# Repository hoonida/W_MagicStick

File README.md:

# MagicStick

## 1. Hardware

### [Arduino Pro Micro](https://www.sparkfun.com/products/12640)

| pin | func | name          |
|-----|------|---------------|
| 2   | DIN  | IR Receive    |
| 3   | DOUT | IR Send       |
| 7   | DIN  | Button        |
| 14  | DOUT | LED 0         |
| 15  | DOUT | LED 1         |
| 16  | DOUT | Relay         |
| 9   | PWM  | Speaker -     |
| 10  | PWM  | Speaker +     |
| A0  | AIN  | Potentiometer |

### Power
- Battery : LR45(1.5V) x 3EA
- Voltage : 4.5V
- Capacity : 45mAh

## 2. Software

### State Machine

| state    | task                             |
|----------|----------------------------------|
| waiting  | receive IR                       |
| sending  | send IR & blink LED & play sound |
| ceremony | blink LED                        |

### Dependencies
- [IRremote (3.6.1)](https://github.com/Arduino-IRremote/Arduino-IRremote)
- [TaskScheduler (3.6.0)](https://github.com/arkhipenko/TaskScheduler)

## 3. References
[NEC Infrared Transmission Protocol](https://techdocs.altium.com/display/FPGA/NEC+Infrared+Transmission+Protocol)

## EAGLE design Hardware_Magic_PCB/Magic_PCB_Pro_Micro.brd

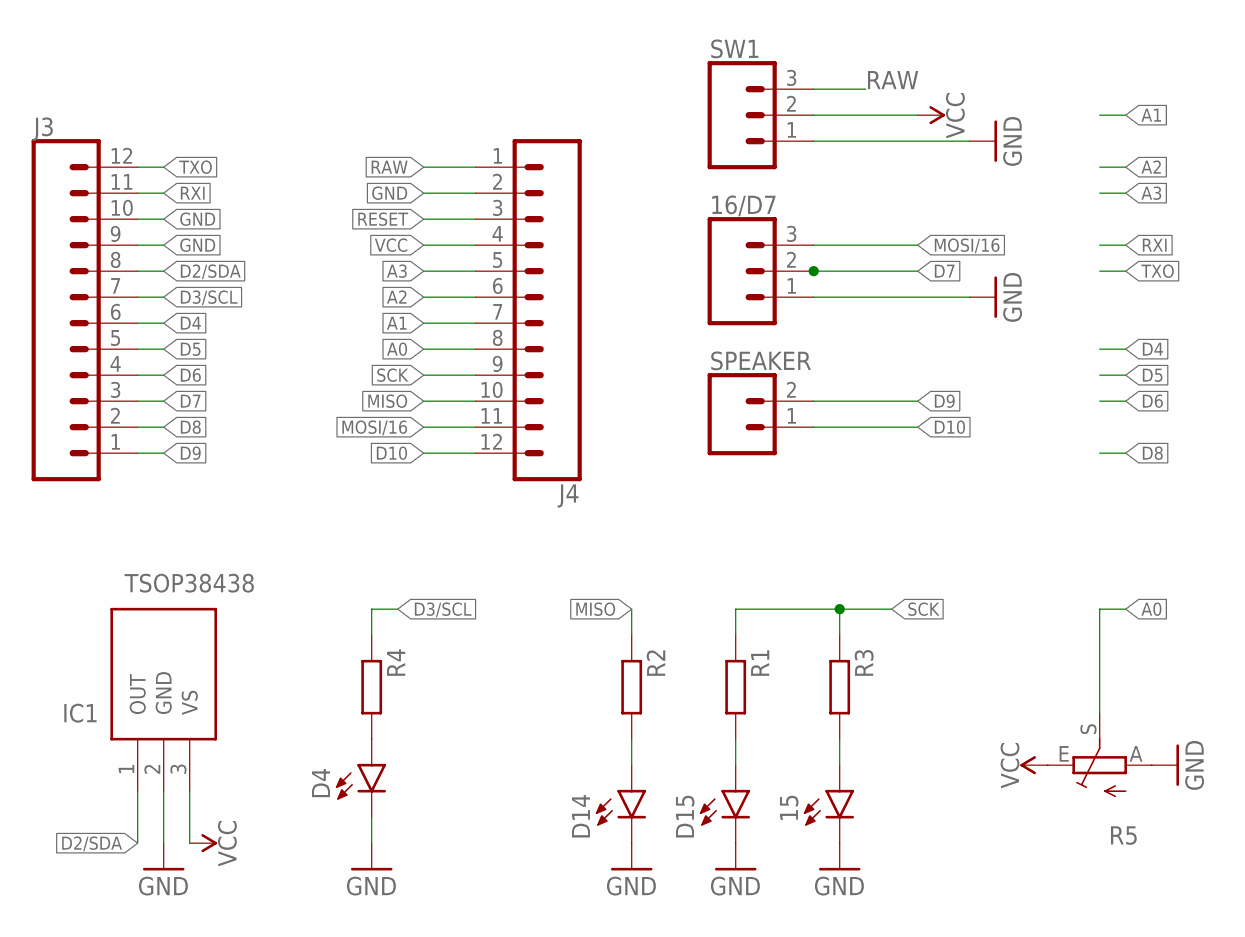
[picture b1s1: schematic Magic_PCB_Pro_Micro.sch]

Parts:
15: GREEN; SFH482
16/D7: CONN_03; 1X03
D4, D14: GREEN; SFH482
D15: Yellow; SFH482
IC1: TSOP38438; TSOP38238
J3, J4: CONN_12LONGPADS; 1X12_LONGPADS
R1, R2, R3: 160; R3216W
R4: 68; R3216W
R5: TRIM_EU-S64W; S64W
SPEAKER: CONN_02; 1X02
SW1: CONN_03; 1X03

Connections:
A0: J4.8, R5.S
A1: J4.7
A2: J4.6
A3: J4.5
D2/SDA: IC1.1 (OUT), J3.8
D3/SCL: J3.7, R4.1
D4: J3.6
D5: J3.5
D6: J3.4
D7: 16/D7.2, J3.3
D8: J3.2
D9: J3.1, SPEAKER.2
D10: J4.12, SPEAKER.1
GND: 15.K (C), 16/D7.1, D4.K (C), D14.K (C), D15.K (C), IC1.2 (GND), J3.9, J3.10, J4.2, R5.A, SW1.1
MISO: J4.10, R2.1
MOSI/16: 16/D7.3, J4.11
unnamed: D14.A, R2.2
unnamed: D15.A, R1.2
unnamed: 15.A, R3.2
unnamed: D4.A, R4.2
RAW: J4.1, SW1.3
RESET: J4.3
RXI: J3.11
SCK: J4.9, R1.1, R3.1
TXO: J3.12
VCC: IC1.3 (VS), J4.4, R5.E, SW1.2

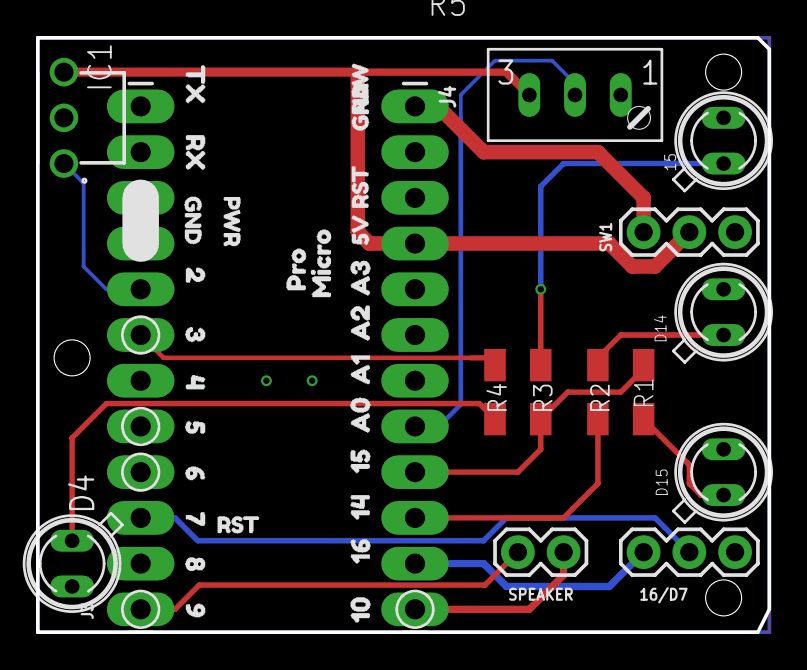
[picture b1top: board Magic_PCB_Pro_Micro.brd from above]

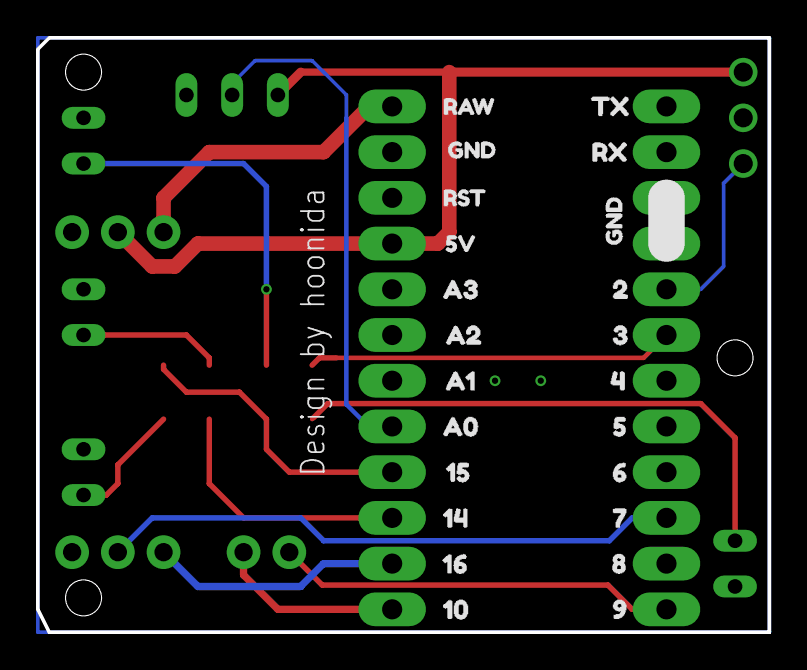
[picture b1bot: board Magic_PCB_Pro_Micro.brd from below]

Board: 2 copper layers, 40.6 x 33.0 mm, 65 parts (23 on the bottom side), 16 nets.

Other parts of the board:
U$2, U$38: 156
U$4, U$48: 164
U$5, U$57: 218
U$6, U$56: 317
U$7, U$54: 515
U$8, U$53: 614
U$9, U$52: 713
U$10, U$51: 812
U$11, U$22, U$32, U$58: GND4
U$12, U$46: RAW5
U$13, U$55: 45
U$16, U$50: 911
U$17, U$37: A07
U$18, U$60: TX2
U$19, U$36: A18
U$21, U$49: 104
U$23: MICRO1
U$24: PRO0
U$25, U$31, U$41: RST3
U$26, U$35: A29
U$27, U$34: A310
U$28, U$59: RX20
U$29, U$47: 145
U$63: PWR0
U$64, U$65: 5V1

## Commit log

2022-05-22 pcb+soft

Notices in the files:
parts and their libraries:
SparkFun-Connectors: Licensing: Creative Commons ShareAlike 4.0 International - https://creativecommons.org/licenses/by-sa/4.0
